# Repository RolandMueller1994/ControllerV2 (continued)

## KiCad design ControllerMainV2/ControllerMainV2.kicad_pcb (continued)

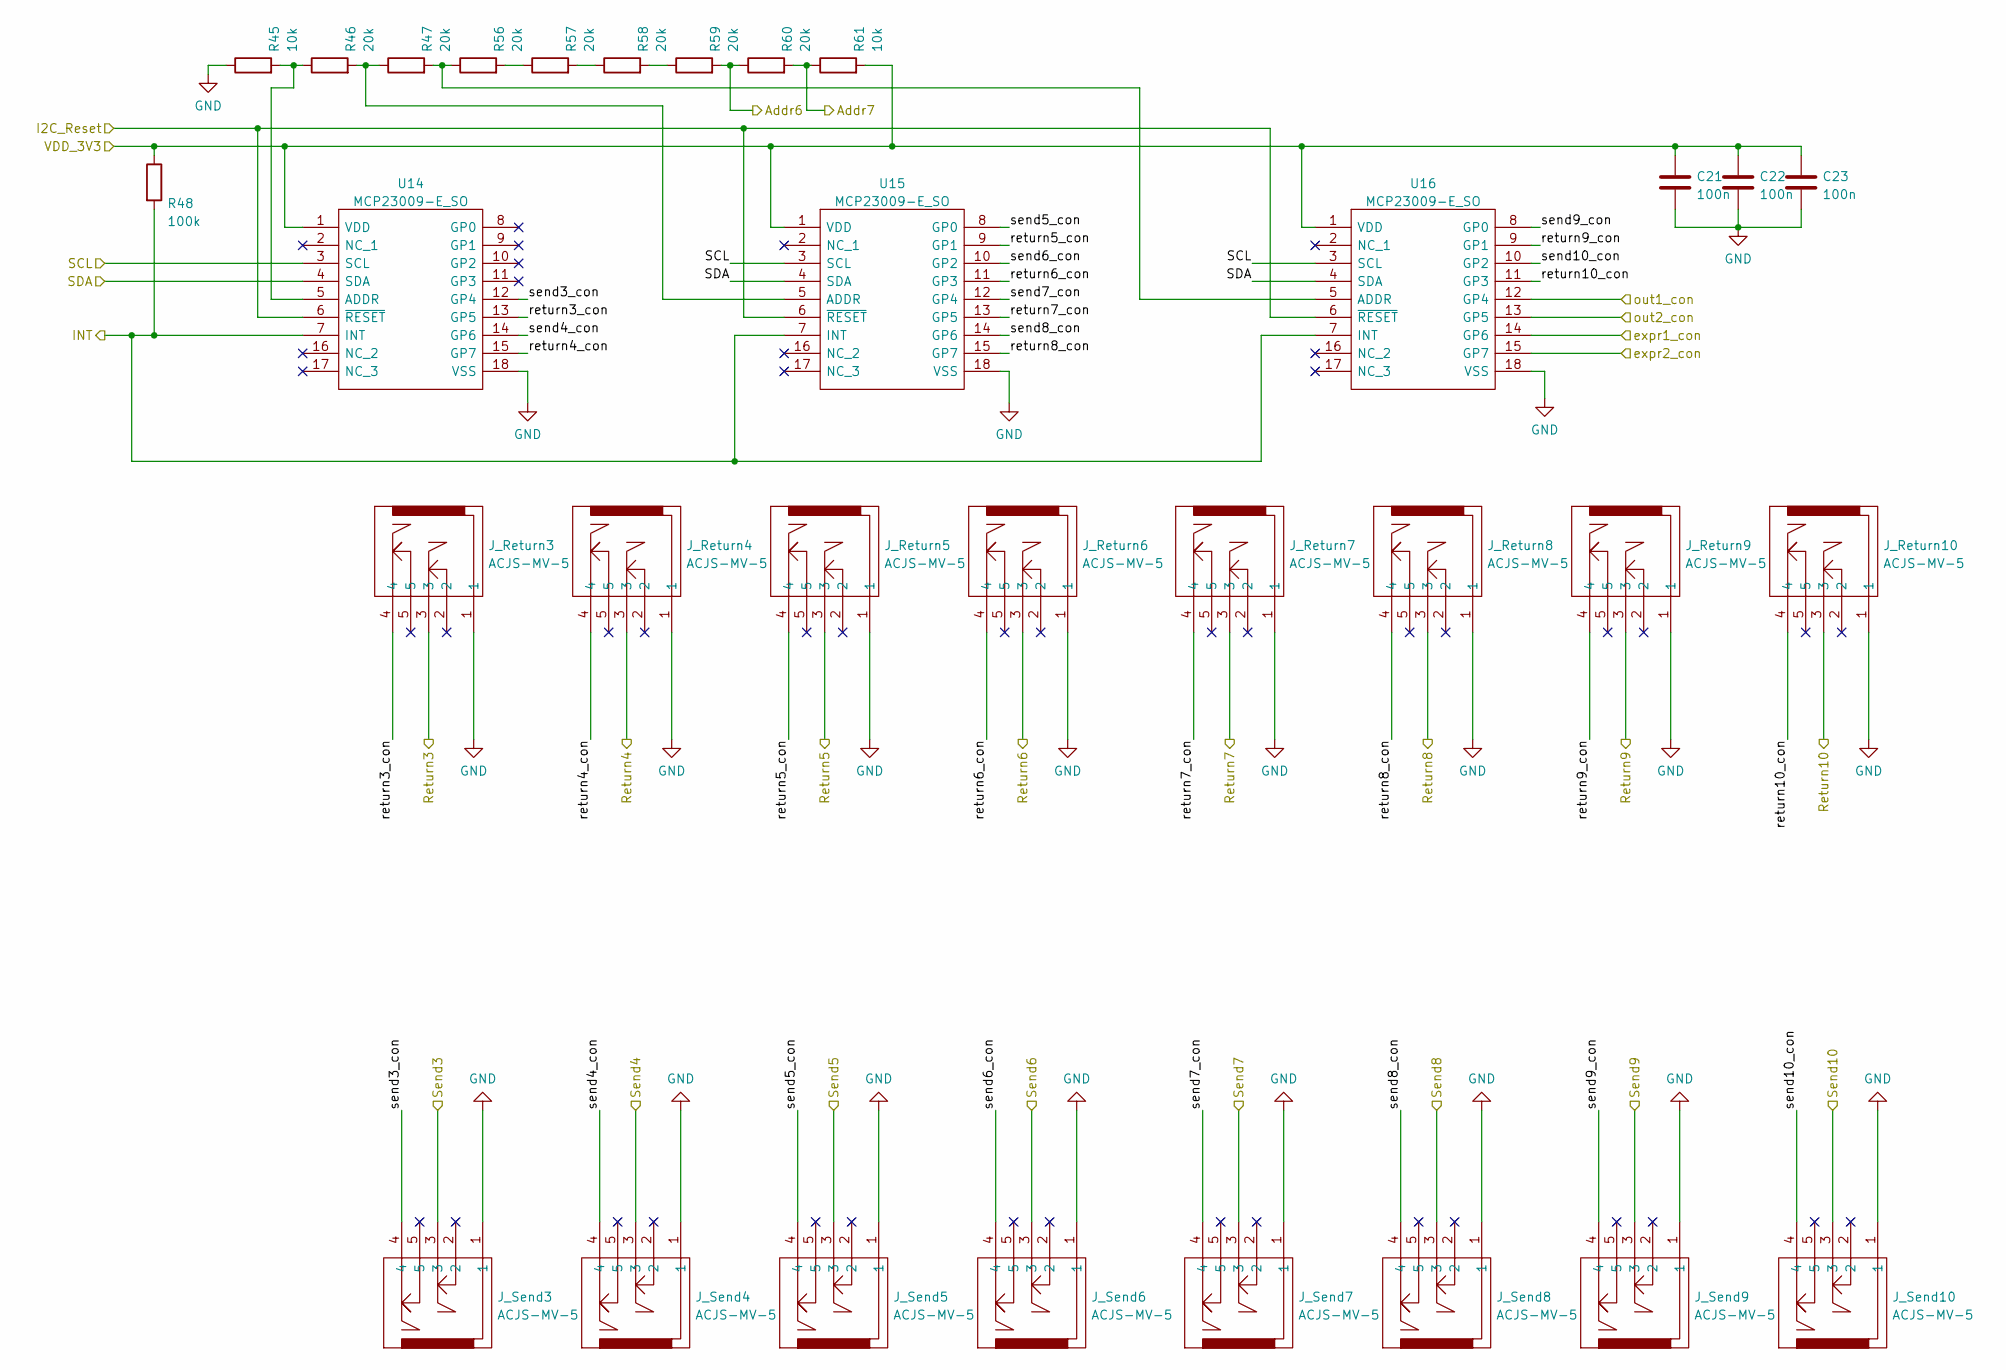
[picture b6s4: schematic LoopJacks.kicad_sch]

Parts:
C21, C22, C23: 100n; C_1206_3216Metric_Pad1.33x1.80mm_HandSolder
J_Return3, J_Return4, J_Return5, J_Return6, J_Return7, J_Return8, J_Return9, J_Return10: ACJS-MV-5; ACJSMV5; Manufacturer_Part_Number ACJS-MV-5; Mouser Part Number 523-ACJS-MV-5
J_Send3, J_Send4, J_Send5, J_Send6, J_Send7, J_Send8, J_Send9, J_Send10: ACJS-MV-5; ACJSMV5; Manufacturer_Part_Number ACJS-MV-5; Mouser Part Number 523-ACJS-MV-5
R45, R61: 10k; R_1206_3216Metric_Pad1.30x1.75mm_HandSolder
R46, R47, R56, R57, R58, R59, R60: 20k; R_1206_3216Metric_Pad1.30x1.75mm_HandSolder
R48: 100k; R_1206_3216Metric_Pad1.30x1.75mm_HandSolder
U14, U15, U16: MCP23009-E_SO; SOIC127P1030X265-18N; Manufacturer_Part_Number MCP23009-E/SO; Mouser Part Number 579-MCP23009-E/SO

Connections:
/Addr6: R59.2, R60.1; also elsewhere on the board
/Addr7: R60.2, R61.1; also elsewhere on the board
/INT: R48.2, U14.7 (INT), U15.7 (INT), U16.7 (INT); also elsewhere on the board
/LoopJacks/expr1_con: U16.14 (GP6); also elsewhere on the board
/LoopJacks/expr2_con: U16.15 (GP7); also elsewhere on the board
/LoopJacks/out1_con: U16.12 (GP4); also elsewhere on the board
/LoopJacks/out2_con: U16.13 (GP5); also elsewhere on the board
/LoopJacks/return3_con: J_Return3.4, U14.13 (GP5)
/LoopJacks/return4_con: J_Return4.4, U14.15 (GP7)
/LoopJacks/return5_con: J_Return5.4, U15.9 (GP1)
/LoopJacks/return6_con: J_Return6.4, U15.11 (GP3)
/LoopJacks/return7_con: J_Return7.4, U15.13 (GP5)
/LoopJacks/return8_con: J_Return8.4, U15.15 (GP7)
/LoopJacks/return9_con: J_Return9.4, U16.9 (GP1)
/LoopJacks/return10_con: J_Return10.4, U16.11 (GP3)
/LoopJacks/send3_con: J_Send3.4, U14.12 (GP4)
/LoopJacks/send4_con: J_Send4.4, U14.14 (GP6)
/LoopJacks/send5_con: J_Send5.4, U15.8 (GP0)
/LoopJacks/send6_con: J_Send6.4, U15.10 (GP2)
/LoopJacks/send7_con: J_Send7.4, U15.12 (GP4)
/LoopJacks/send8_con: J_Send8.4, U15.14 (GP6)
/LoopJacks/send9_con: J_Send9.4, U16.8 (GP0)
/LoopJacks/send10_con: J_Send10.4, U16.10 (GP2)
/SCL: U14.3 (SCL), U15.3 (SCL), U16.3 (SCL); also elsewhere on the board
/SDA: U14.4 (SDA), U15.4 (SDA), U16.4 (SDA); also elsewhere on the board
/return3: J_Return3.3; also elsewhere on the board
/return4: J_Return4.3; also elsewhere on the board
/return5: J_Return5.3; also elsewhere on the board
/return6: J_Return6.3; also elsewhere on the board
/return7: J_Return7.3; also elsewhere on the board
/return8: J_Return8.3; also elsewhere on the board
/return9: J_Return9.3; also elsewhere on the board
/return10: J_Return10.3; also elsewhere on the board
/send3: J_Send3.3; also elsewhere on the board
/send4: J_Send4.3; also elsewhere on the board
/send5: J_Send5.3; also elsewhere on the board
/send6: J_Send6.3; also elsewhere on the board
/send7: J_Send7.3; also elsewhere on the board
/send8: J_Send8.3; also elsewhere on the board
/send9: J_Send9.3; also elsewhere on the board
/send10: J_Send10.3; also elsewhere on the board
unnamed: R45.2, R46.1, U14.5 (ADDR)
unnamed: R46.2, R47.1, U15.5 (ADDR)
unnamed: R47.2, R56.1, U16.5 (ADDR)
unnamed: R56.2, R57.1
unnamed: R57.2, R58.1
unnamed: R58.2, R59.1

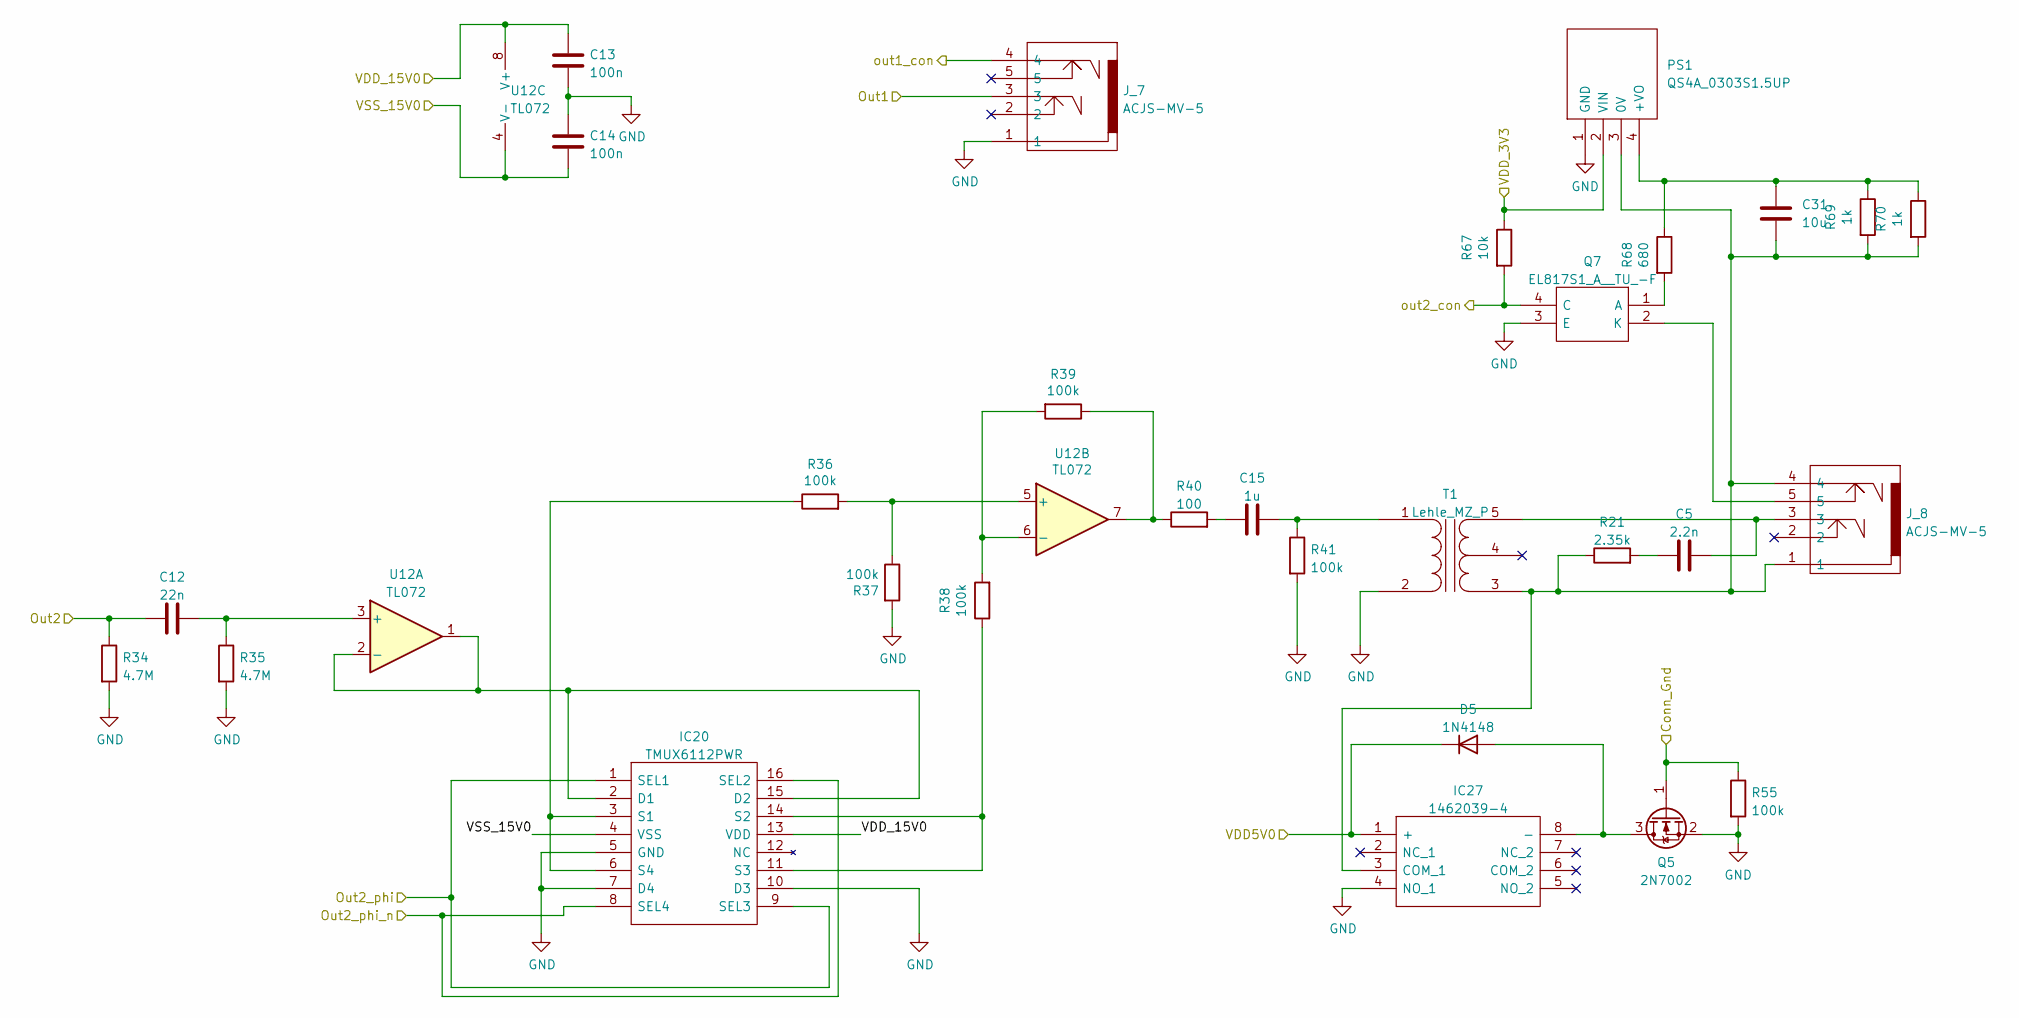
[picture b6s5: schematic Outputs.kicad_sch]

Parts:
C5: 2.2n; C_1206_3216Metric_Pad1.33x1.80mm_HandSolder
C12: 22n; C_1206_3216Metric_Pad1.33x1.80mm_HandSolder
C13, C14: 100n; C_1206_3216Metric_Pad1.33x1.80mm_HandSolder
C15: 1u; C_1206_3216Metric_Pad1.33x1.80mm_HandSolder
C31: 10u; C_1206_3216Metric_Pad1.33x1.80mm_HandSolder
D5: 1N4148; D_SOD-123
IC20: TMUX6112PWR; SOP65P640X120-16N; Manufacturer_Part_Number TMUX6112PWR; Mouser Part Number 595-TMUX6112PWR
IC27: 1462039-4; 14620394; Manufacturer_Part_Number 1462039-4; Mouser Part Number 655-1462039-4
J_7, J_8: ACJS-MV-5; ACJSMV5; Manufacturer_Part_Number ACJS-MV-5; Mouser Part Number 523-ACJS-MV-5
PS1: QS4A_0303S1.5UP; QS4A_1.5UP; Manufacturer_Part_Number QS4A_0303S1.5UP
Q5: 2N7002; SOT-23
Q7: EL817S1_A__TU_-F; SOP254P1030X390-4N; Manufacturer_Part_Number EL817S1(A)(TU)-F
R21: 2.35k; R_1206_3216Metric_Pad1.30x1.75mm_HandSolder
R34, R35: 4.7M; R_1206_3216Metric_Pad1.30x1.75mm_HandSolder
R36, R37, R38, R39, R41, R55: 100k; R_1206_3216Metric_Pad1.30x1.75mm_HandSolder
R40: 100; R_1206_3216Metric_Pad1.30x1.75mm_HandSolder
R67: 10k; R_1206_3216Metric_Pad1.30x1.75mm_HandSolder
R68: 680; R_1206_3216Metric_Pad1.30x1.75mm_HandSolder
R69, R70: 1k; R_1206_3216Metric_Pad1.30x1.75mm_HandSolder
T1: Lehle_MZ_P
U12: TL072; SOIC127P600X175-8N

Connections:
/LoopJacks/out1_con: J_7.4; also elsewhere on the board
/LoopJacks/out2_con: Q7.4 (C), R67.2; also elsewhere on the board
/Out2_phi: IC20.1 (SEL1), IC20.9 (SEL3); also elsewhere on the board
/Out2_phi_n: IC20.8 (SEL4), IC20.16 (SEL2); also elsewhere on the board
/Outputs/Conn_Gnd: Q5.1 (G), R55.1; also elsewhere on the board
/out1: J_7.3; also elsewhere on the board
/out2: C12.1, R34.1; also elsewhere on the board
unnamed: C5.1, J_8.3, T1.5 (SB)
unnamed: C5.2, R21.2
unnamed: C12.2, R35.1, U12.3 (+)
unnamed: C15.1, R40.2
unnamed: C15.2, R41.1, T1.1 (AA)
unnamed: C31.1, IC27.3 (COM_1), J_8.1, J_8.4, PS1.3 (0V), R21.1, R69.2, R70.2, T1.3 (SA)
unnamed: C31.2, PS1.4 (+VO), R68.1, R69.1, R70.1
unnamed: D5.2 (A), IC27.8 (-), Q5.3 (D)
unnamed: IC20.3 (S1), IC20.6 (S4), R36.1
unnamed: IC20.11 (S3), IC20.14 (S2), R38.1
unnamed: IC20.2 (D1), IC20.15 (D2), U12.1, U12.2 (-)
unnamed: J_8.5, Q7.2 (K)
unnamed: Q7.1 (A), R68.2
unnamed: R36.2, R37.1, U12.5 (+)
unnamed: R38.2, R39.2, U12.6 (-)
unnamed: R39.1, R40.1, U12.7

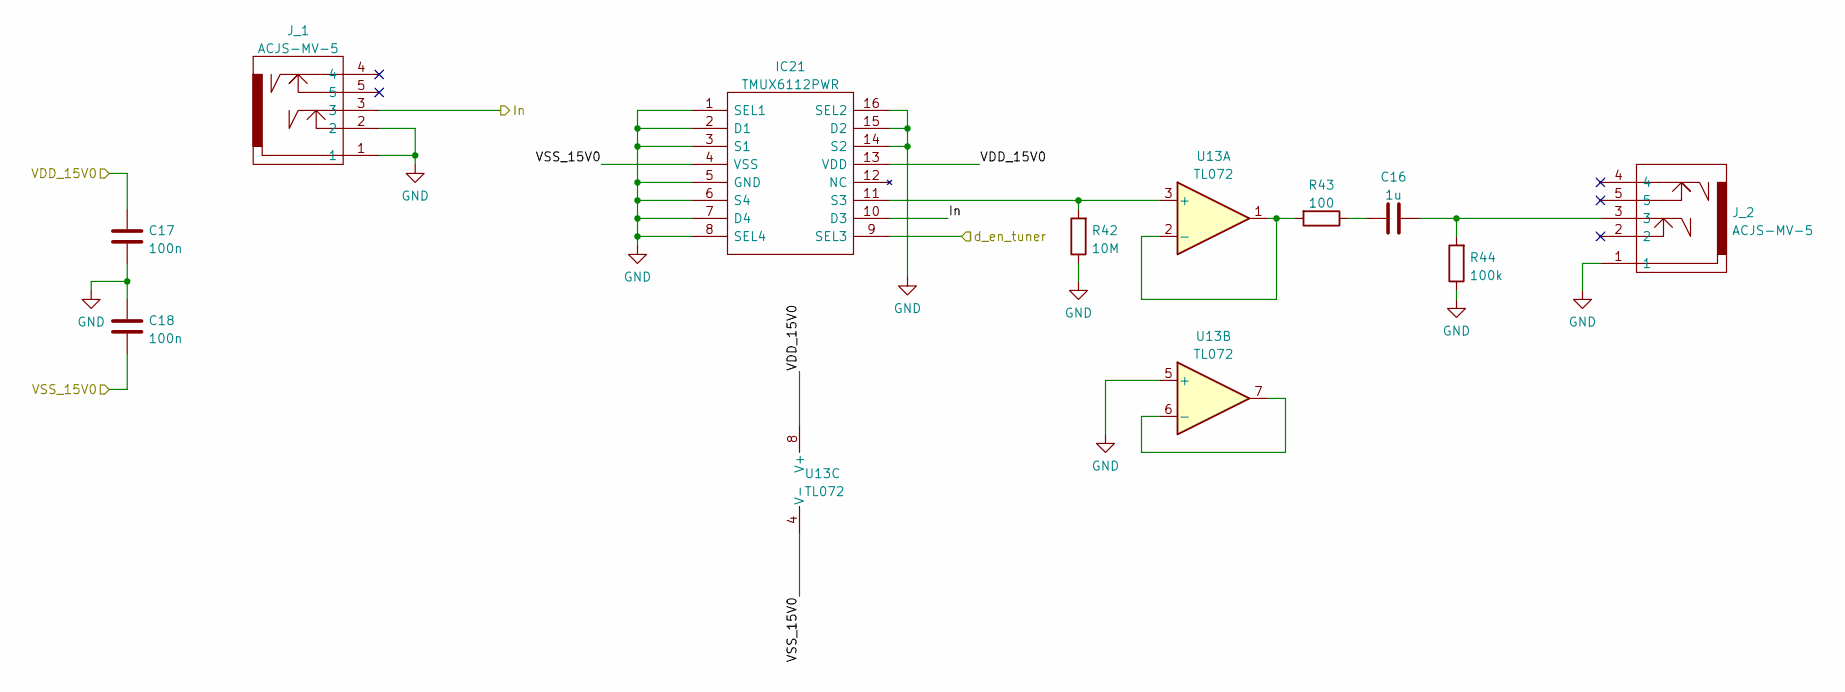
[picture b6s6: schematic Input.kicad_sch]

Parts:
C16: 1u; C_1206_3216Metric_Pad1.33x1.80mm_HandSolder
C17, C18: 100n; C_1206_3216Metric_Pad1.33x1.80mm_HandSolder
IC21: TMUX6112PWR; SOP65P640X120-16N; Manufacturer_Part_Number TMUX6112PWR; Mouser Part Number 595-TMUX6112PWR
J_1, J_2: ACJS-MV-5; ACJSMV5; Manufacturer_Part_Number ACJS-MV-5; Mouser Part Number 523-ACJS-MV-5
R42: 10M; R_1206_3216Metric_Pad1.30x1.75mm_HandSolder
R43: 100; R_1206_3216Metric_Pad1.30x1.75mm_HandSolder
R44: 100k; R_1206_3216Metric_Pad1.30x1.75mm_HandSolder
U13: TL072; SOIC127P600X175-8N

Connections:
/Tuner: IC21.9 (SEL3); also elsewhere on the board
/in: IC21.10 (D3), J_1.3; also elsewhere on the board
unnamed: C16.1, R43.1
unnamed: C16.2, J_2.3, R44.2
unnamed: IC21.11 (S3), R42.2, U13.3 (+)
unnamed: R43.2, U13.1, U13.2 (-)
unnamed: U13.6 (-), U13.7

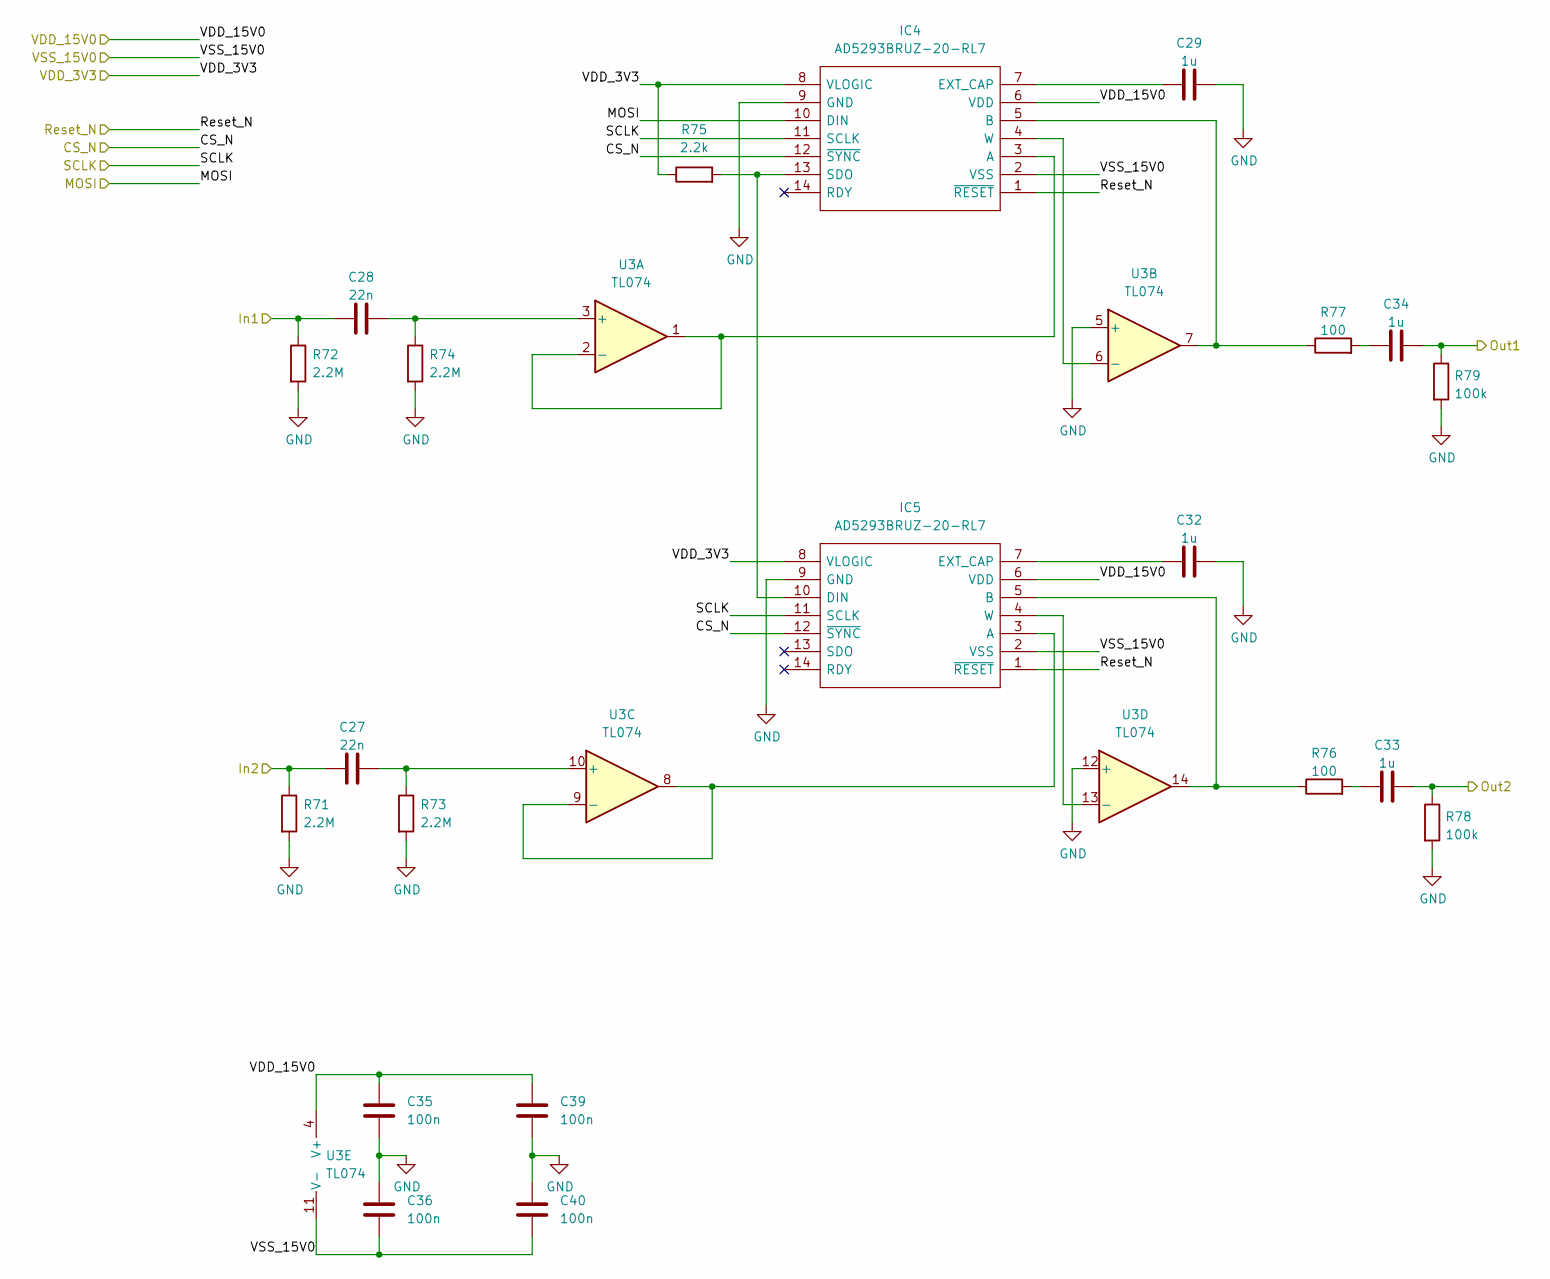
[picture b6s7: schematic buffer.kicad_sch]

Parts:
C27, C28: 22n; C_1206_3216Metric_Pad1.33x1.80mm_HandSolder
C29, C32, C33, C34: 1u; C_1206_3216Metric_Pad1.33x1.80mm_HandSolder
C35, C36, C39, C40: 100n; C_1206_3216Metric_Pad1.33x1.80mm_HandSolder
IC4, IC5: AD5293BRUZ-20-RL7; SOP65P640X120-14N; Manufacturer_Part_Number AD5293BRUZ-20-RL7; Mouser Part Number 584-AD5293BRUZ-20-R7
R71, R72, R73, R74: 2.2M; R_1206_3216Metric_Pad1.30x1.75mm_HandSolder
R75: 2.2k; R_1206_3216Metric_Pad1.30x1.75mm_HandSolder
R76, R77: 100; R_1206_3216Metric_Pad1.30x1.75mm_HandSolder
R78, R79: 100k; R_1206_3216Metric_Pad1.30x1.75mm_HandSolder
U3: TL074; SOIC127P600X175-14N

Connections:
/MOSI: IC4.10 (DIN); also elsewhere on the board
/SCLK: IC4.11 (SCLK), IC5.11 (SCLK); also elsewhere on the board
/amp1: C28.1, R72.1; also elsewhere on the board
/amp1_out: C34.2, R79.1; also elsewhere on the board
/amp2: C27.1, R71.1; also elsewhere on the board
/amp2_out: C33.2, R78.1; also elsewhere on the board
unnamed: C27.2, R73.1, U3.10 (+)
unnamed: C28.2, R74.1, U3.3 (+)
unnamed: C29.1, IC4.7 (EXT_CAP)
unnamed: C32.1, IC5.7 (EXT_CAP)
unnamed: C33.1, R76.2
unnamed: C34.1, R77.2
unnamed: IC4.3 (A), U3.1, U3.2 (-)
unnamed: IC4.4 (W), U3.6 (-)
unnamed: IC4.5 (B), R77.1, U3.7
unnamed: IC4.13 (SDO), IC5.10 (DIN), R75.2
unnamed: IC5.3 (A), U3.8, U3.9 (-)
unnamed: IC5.4 (W), U3.13 (-)
unnamed: IC5.5 (B), R76.1, U3.14

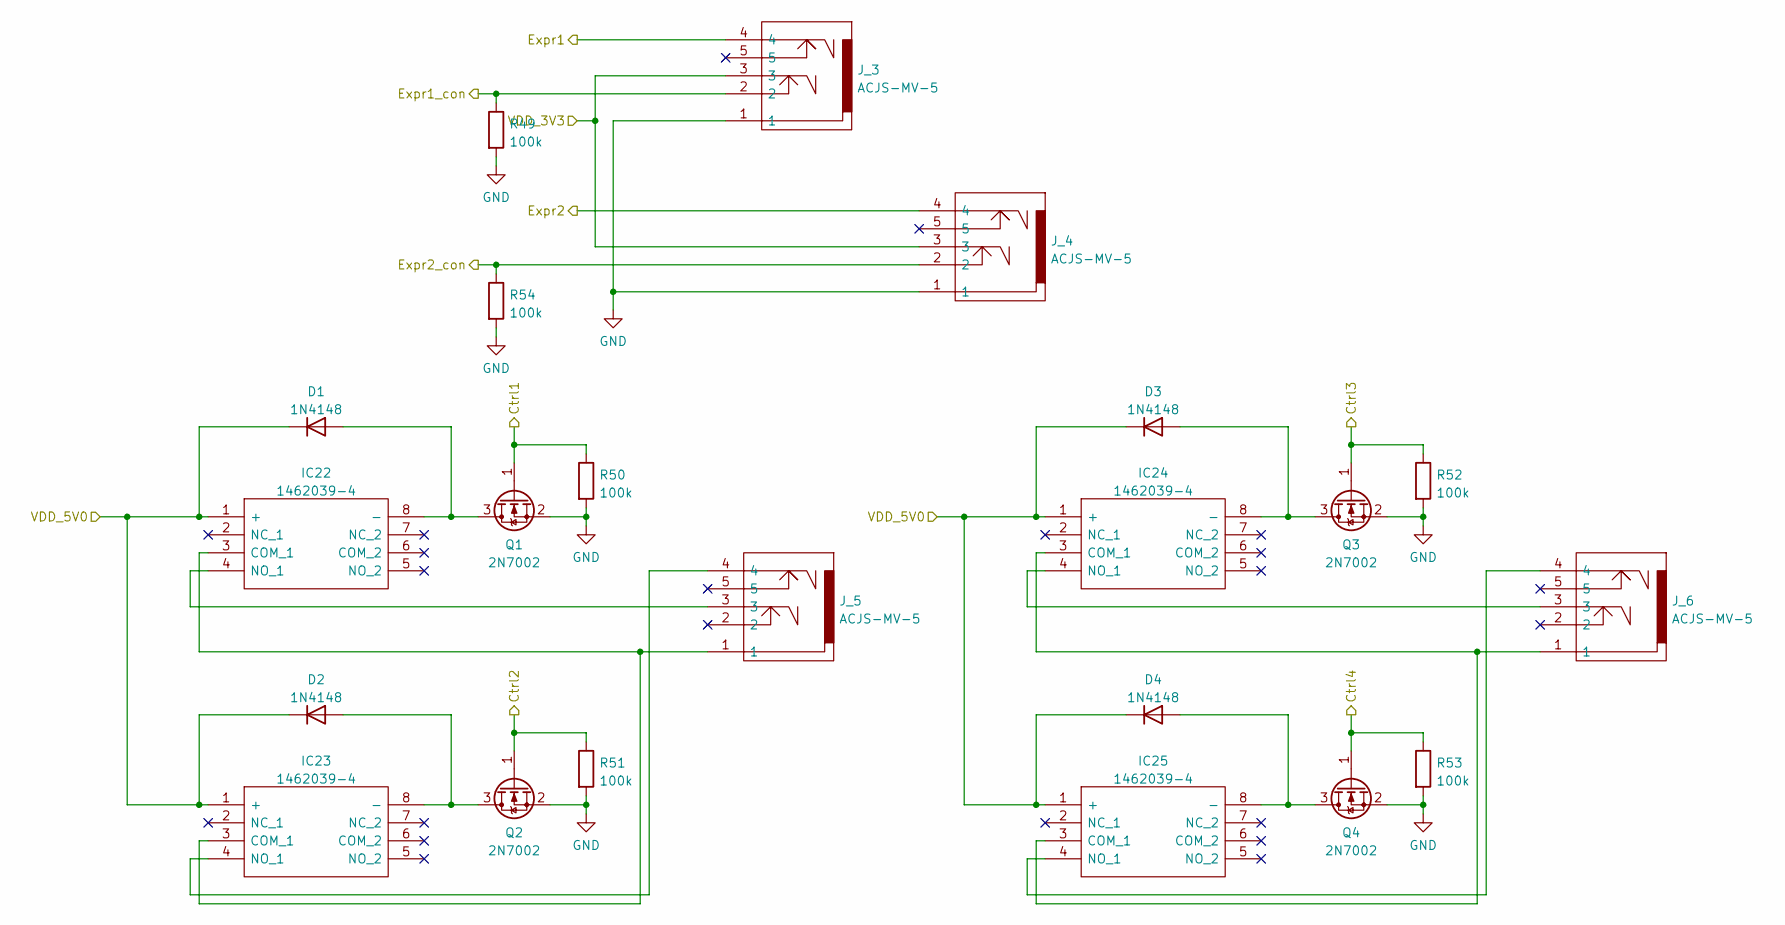
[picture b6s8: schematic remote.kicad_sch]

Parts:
D1, D2, D3, D4: 1N4148; D_SOD-123
IC22, IC23, IC24, IC25: 1462039-4; 14620394; Manufacturer_Part_Number 1462039-4; Mouser Part Number 655-1462039-4
J_3, J_4, J_5, J_6: ACJS-MV-5; ACJSMV5; Manufacturer_Part_Number ACJS-MV-5; Mouser Part Number 523-ACJS-MV-5
Q1, Q2, Q3, Q4: 2N7002; SOT-23
R49, R50, R51, R52, R53, R54: 100k; R_1206_3216Metric_Pad1.30x1.75mm_HandSolder

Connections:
/Ctrl1: Q1.1 (G), R50.1; also elsewhere on the board
/Ctrl2: Q2.1 (G), R51.1; also elsewhere on the board
/Ctrl3: Q3.1 (G), R52.1; also elsewhere on the board
/Ctrl4: Q4.1 (G), R53.1; also elsewhere on the board
/LoopJacks/expr1_con: J_3.2, R49.1; also elsewhere on the board
/LoopJacks/expr2_con: J_4.2, R54.1; also elsewhere on the board
/expr1: J_3.4; also elsewhere on the board
/expr2: J_4.4; also elsewhere on the board
unnamed: D1.2 (A), IC22.8 (-), Q1.3 (D)
unnamed: D2.2 (A), IC23.8 (-), Q2.3 (D)
unnamed: D3.2 (A), IC24.8 (-), Q3.3 (D)
unnamed: D4.2 (A), IC25.8 (-), Q4.3 (D)
unnamed: IC22.3 (COM_1), IC23.3 (COM_1), J_5.1
unnamed: IC22.4 (NO_1), J_5.3
unnamed: IC23.4 (NO_1), J_5.4
unnamed: IC24.3 (COM_1), IC25.3 (COM_1), J_6.1
unnamed: IC24.4 (NO_1), J_6.3
unnamed: IC25.4 (NO_1), J_6.4

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
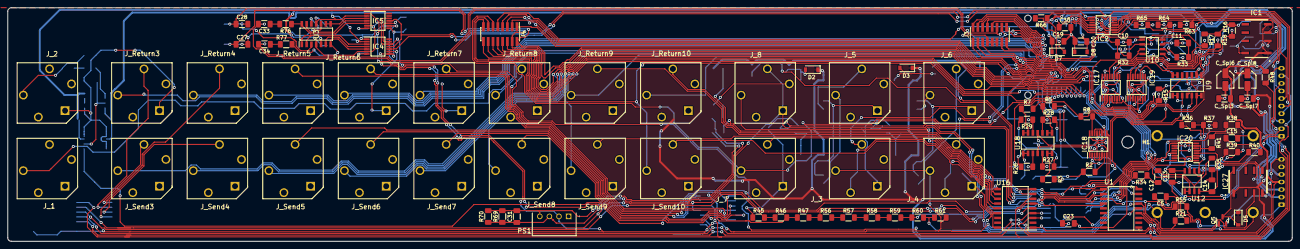
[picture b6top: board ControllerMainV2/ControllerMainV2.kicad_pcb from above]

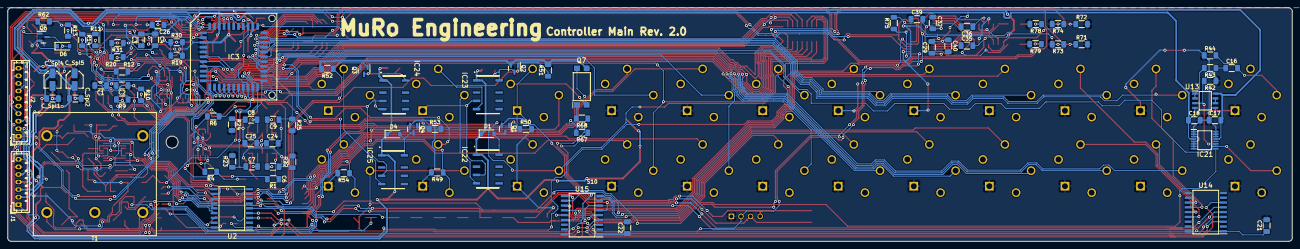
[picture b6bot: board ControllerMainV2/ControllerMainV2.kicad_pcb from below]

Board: 2 copper layers, 340.0 x 61.8 mm, 197 parts (84 on the bottom side), 169 nets.

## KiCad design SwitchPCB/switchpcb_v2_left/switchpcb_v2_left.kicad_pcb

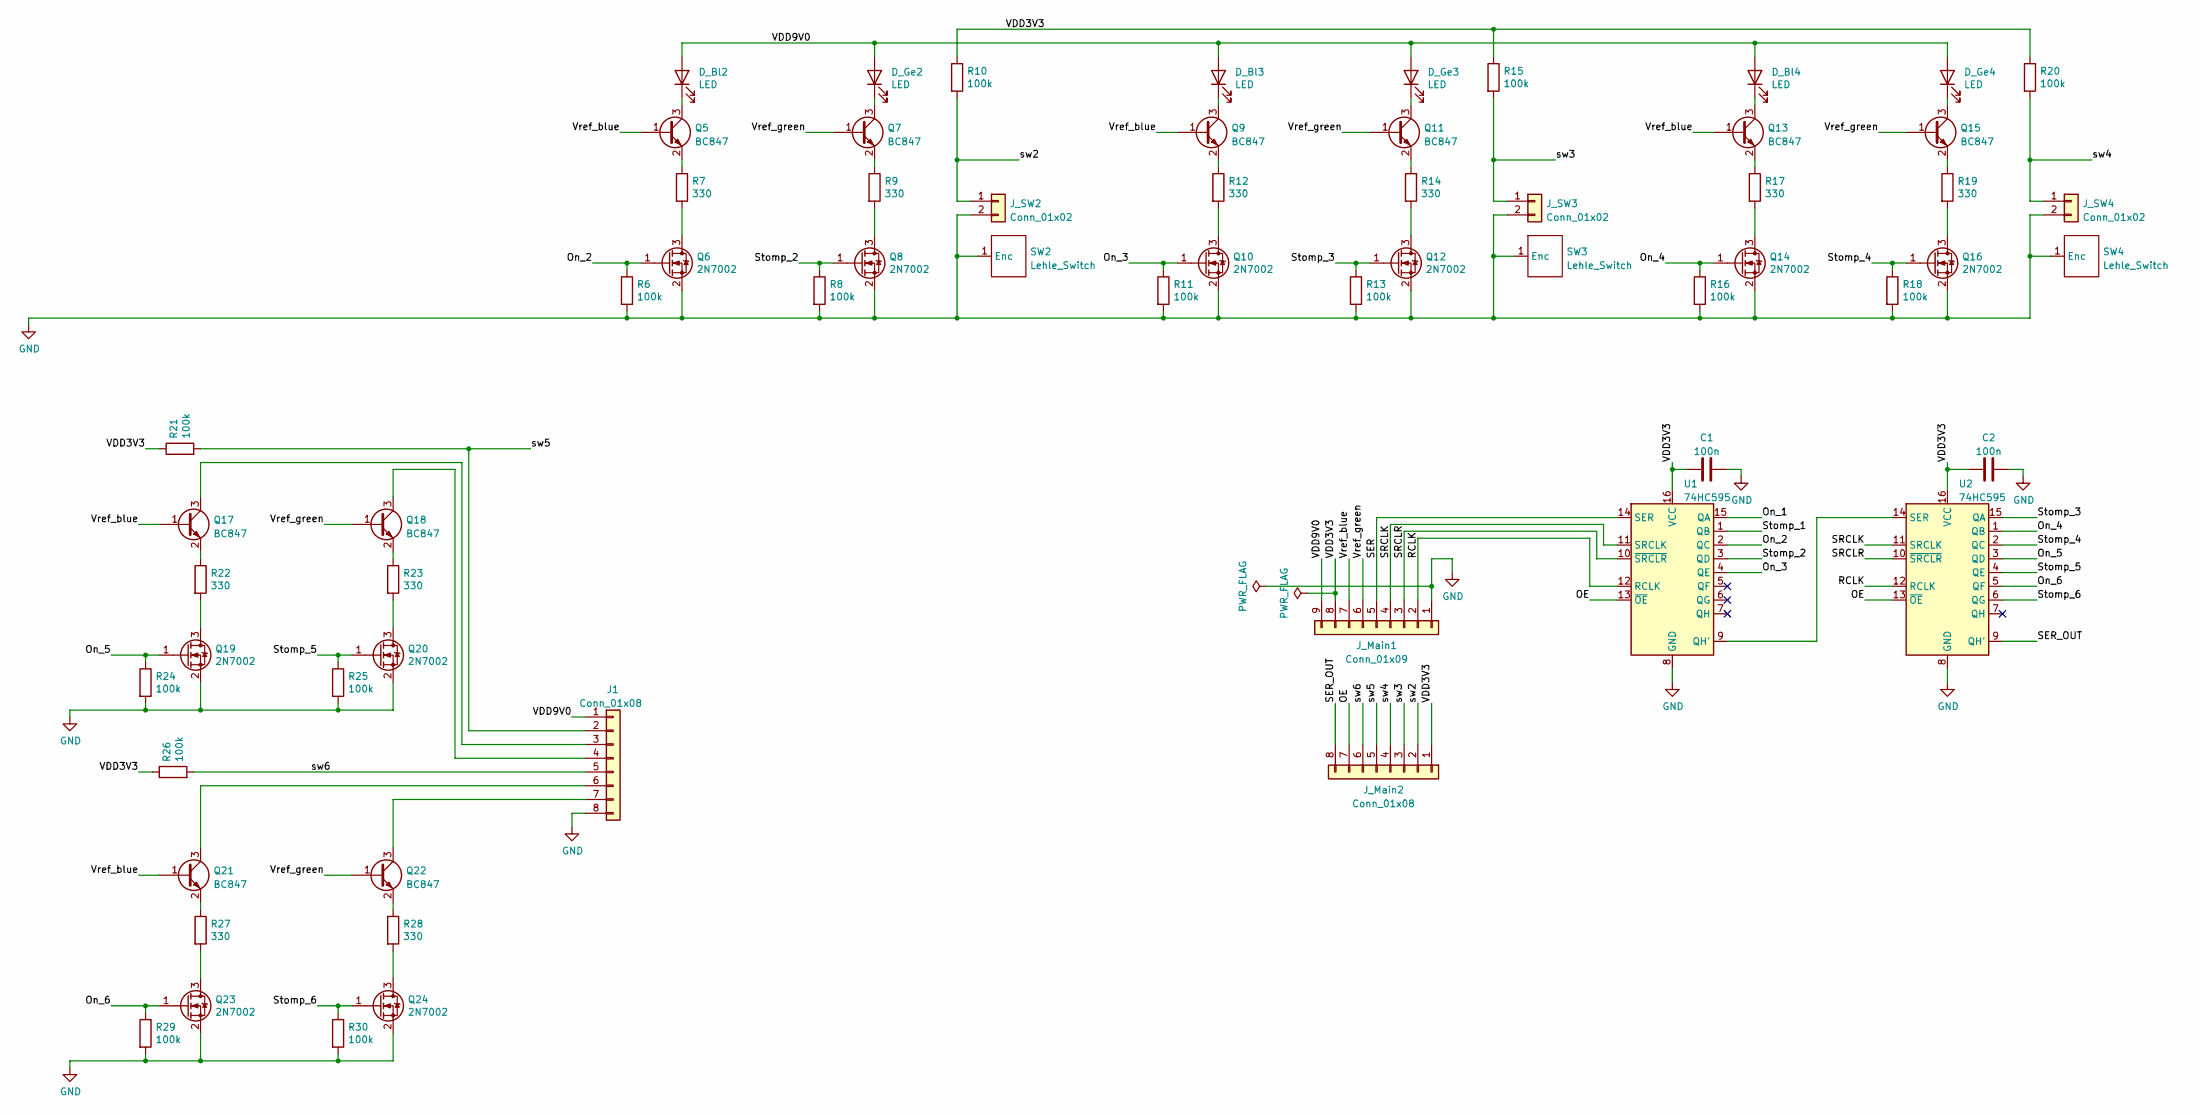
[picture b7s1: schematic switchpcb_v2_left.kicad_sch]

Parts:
C1, C2: 100n; C_1206_3216Metric_Pad1.33x1.80mm_HandSolder
D_Bl2, D_Bl3, D_Bl4: LED; LED_D3.0mm
D_Ge2, D_Ge3, D_Ge4: LED; LED_D3.0mm
J1: Conn_01x08; JST_PH_B8B-PH-K_1x08_P2.00mm_Vertical
J_Main1: Conn_01x09; JST_PH_B9B-PH-K_1x09_P2.00mm_Vertical
J_Main2: Conn_01x08; JST_PH_B8B-PH-K_1x08_P2.00mm_Vertical
J_SW2, J_SW3, J_SW4: Conn_01x02; JST_PH_B2B-PH-K_1x02_P2.00mm_Vertical
Q5, Q7, Q9, Q11, Q13, Q15, Q17, Q18, Q21, Q22: BC847; SOT-23
Q6, Q8, Q10, Q12, Q14, Q16, Q19, Q20, Q23, Q24: 2N7002; SOT-23
R6, R8, R10, R11, R13, R15, R16, R18, R20, R21, R24, R25, R26, R29, R30: 100k; R_1206_3216Metric_Pad1.30x1.75mm_HandSolder
R7, R9, R12, R14, R17, R19, R22, R23, R27, R28: 330; R_1206_3216Metric_Pad1.30x1.75mm_HandSolder
SW2, SW3, SW4: Lehle_Switch; LehleSwitch
U1, U2: 74HC595; SOIC127P600X175-16N

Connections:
/OE: J_Main2.7, U1.13 (~OE), U2.13 (~OE)
/On_1: U1.15 (QA)
/On_2: Q6.1 (G), R6.1, U1.2 (QC)
/On_3: Q10.1 (G), R11.1, U1.4 (QE)
/On_4: Q14.1 (G), R16.1, U2.1 (QB)
/On_5: Q19.1 (G), R24.1, U2.3 (QD)
/On_6: Q23.1 (G), R29.1, U2.5 (QF)
/RCLK: J_Main1.2, U1.12 (RCLK), U2.12 (RCLK)
/SER: J_Main1.5, U1.14 (SER)
/SER_OUT: J_Main2.8, U2.9 (QH')
/SRCLK: J_Main1.4, U1.11 (SRCLK), U2.11 (SRCLK)
/SRCLR: J_Main1.3, U1.10 (~SRCLR), U2.10 (~SRCLR)
/Stomp_1: U1.1 (QB)
/Stomp_2: Q8.1 (G), R8.1, U1.3 (QD)
/Stomp_3: Q12.1 (G), R13.1, U2.15 (QA)
/Stomp_4: Q16.1 (G), R18.1, U2.2 (QC)
/Stomp_5: Q20.1 (G), R25.1, U2.4 (QE)
/Stomp_6: Q24.1 (G), R30.1, U2.6 (QG)
/VDD3V3: C1.1, C2.1, J_Main1.8, J_Main2.1, R10.1, R15.1, R20.1, R21.1, R26.1, U1.16 (VCC), U2.16 (VCC)
/VDD9V0: D_Bl2.2 (A), D_Bl3.2 (A), D_Bl4.2 (A), D_Ge2.2 (A), D_Ge3.2 (A), D_Ge4.2 (A), J1.1, J_Main1.9
/Vref_blue: J_Main1.7, Q5.1 (B), Q9.1 (B), Q13.1 (B), Q17.1 (B), Q21.1 (B)
/Vref_green: J_Main1.6, Q7.1 (B), Q11.1 (B), Q15.1 (B), Q18.1 (B), Q22.1 (B)
/sw2: J_Main2.2, J_SW2.1, R10.2
/sw3: J_Main2.3, J_SW3.1, R15.2
/sw4: J_Main2.4, J_SW4.1, R20.2
/sw5: J1.2, J_Main2.5, R21.2
/sw6: J1.5, J_Main2.6, R26.2
GND: C1.2, C2.2, J1.8, J_Main1.1, J_SW2.2, J_SW3.2, J_SW4.2, Q6.2 (S), Q8.2 (S), Q10.2 (S), Q12.2 (S), Q14.2 (S), Q16.2 (S), Q19.2 (S), Q20.2 (S), Q23.2 (S), Q24.2 (S), R6.2, R8.2, R11.2, R13.2, R16.2, R18.2, R24.2, R25.2, R29.2, R30.2, SW2.1 (Enc), SW3.1 (Enc), SW4.1 (Enc), U1.8 (GND), U2.8 (GND)
unnamed: D_Bl2.1 (K), Q5.3 (C)
unnamed: D_Bl3.1 (K), Q9.3 (C)
unnamed: D_Bl4.1 (K), Q13.3 (C)
unnamed: D_Ge2.1 (K), Q7.3 (C)
unnamed: D_Ge3.1 (K), Q11.3 (C)
unnamed: D_Ge4.1 (K), Q15.3 (C)
unnamed: J1.3, Q17.3 (C)
unnamed: J1.4, Q18.3 (C)
unnamed: J1.6, Q21.3 (C)
unnamed: J1.7, Q22.3 (C)
unnamed: Q5.2 (E), R7.1
unnamed: Q6.3 (D), R7.2
unnamed: Q7.2 (E), R9.1
unnamed: Q8.3 (D), R9.2
unnamed: Q9.2 (E), R12.1
unnamed: Q10.3 (D), R12.2
unnamed: Q11.2 (E), R14.1
unnamed: Q12.3 (D), R14.2
unnamed: Q13.2 (E), R17.1
unnamed: Q14.3 (D), R17.2
unnamed: Q15.2 (E), R19.1
unnamed: Q16.3 (D), R19.2
unnamed: Q17.2 (E), R22.1
unnamed: Q18.2 (E), R23.1
unnamed: Q19.3 (D), R22.2
unnamed: Q20.3 (D), R23.2
unnamed: Q21.2 (E), R27.1
unnamed: Q22.2 (E), R28.1
unnamed: Q23.3 (D), R27.2
unnamed: Q24.3 (D), R28.2
unnamed: U1.9 (QH'), U2.14 (SER)

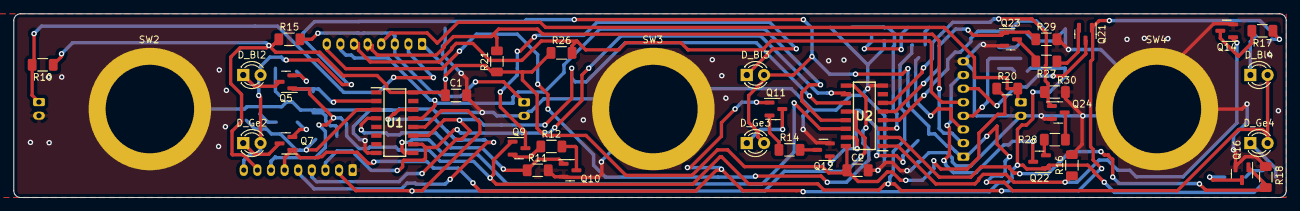
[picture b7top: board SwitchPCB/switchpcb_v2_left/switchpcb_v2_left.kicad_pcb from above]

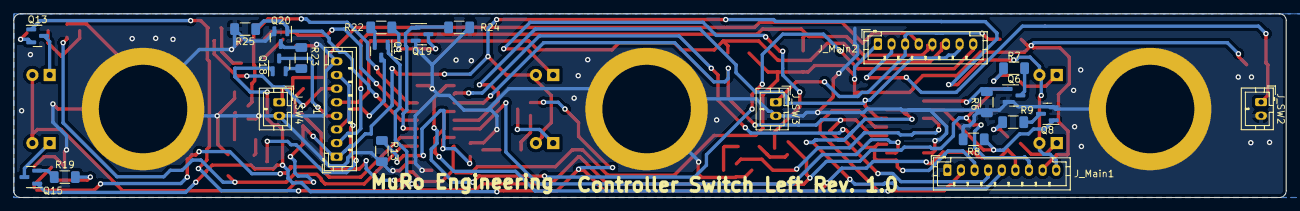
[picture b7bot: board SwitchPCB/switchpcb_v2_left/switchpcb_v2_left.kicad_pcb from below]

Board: 2 copper layers, 187.0 x 27.0 mm, 64 parts (24 on the bottom side), 57 nets.

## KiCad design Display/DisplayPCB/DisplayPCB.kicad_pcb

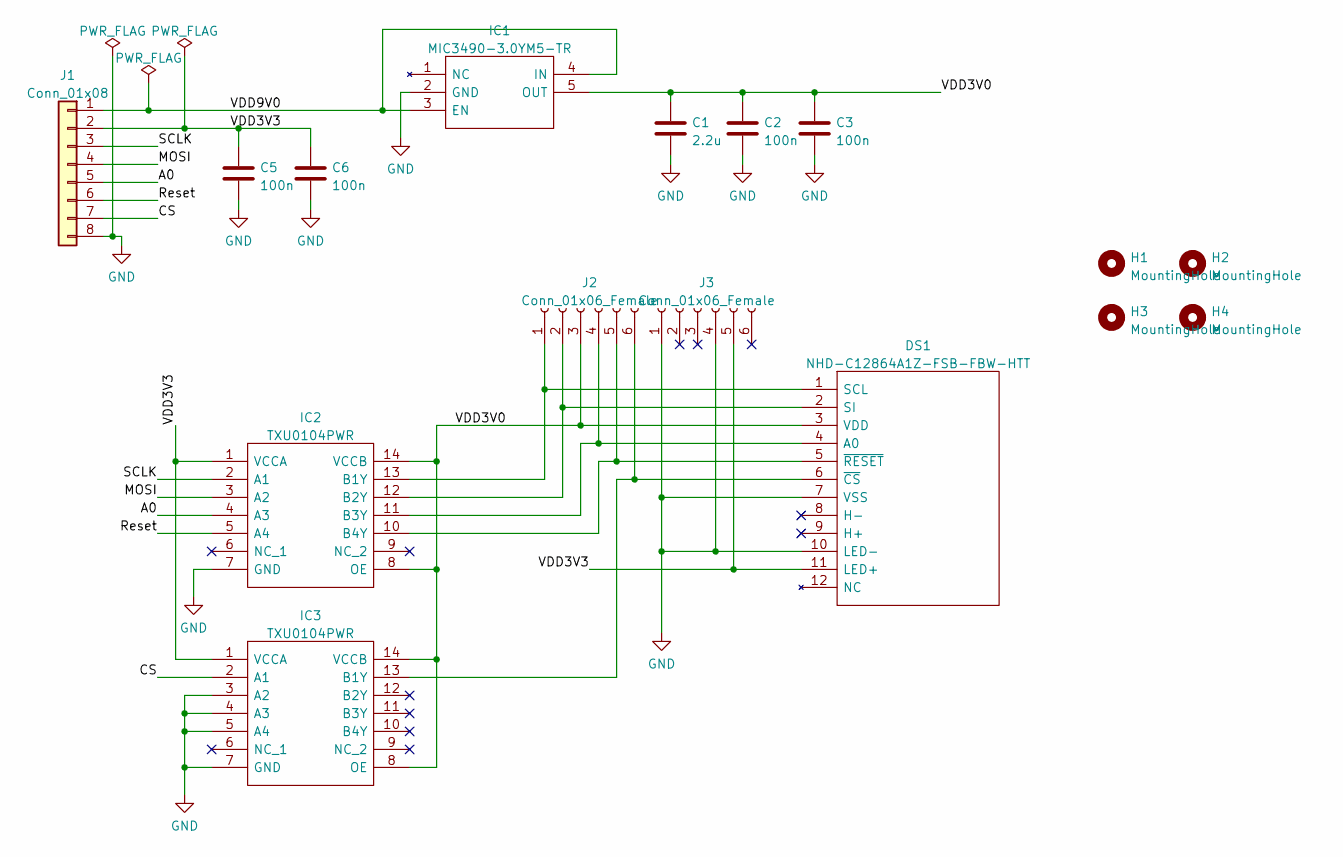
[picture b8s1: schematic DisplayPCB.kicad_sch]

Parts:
C1: 2.2u; C_1206_3216Metric_Pad1.33x1.80mm_HandSolder
C2, C3, C5, C6: 100n; C_1206_3216Metric_Pad1.33x1.80mm_HandSolder
DS1: NHD-C12864A1Z-FSB-FBW-HTT; NHDC12864A1ZFSBFBWHTT; Manufacturer_Part_Number NHD-C12864A1Z-FSB-FBW-HTT; Mouser Part Number 763-C12864A1ZFSBFBWH
H1, H2, H3, H4: MountingHole; MountingHole_3.2mm_M3
IC1: MIC3490-3.0YM5-TR; SOT95P280X145-5N; Manufacturer_Part_Number MIC3490-3.0YM5-TR; Mouser Part Number 579-MIC349030YM5TR
IC2, IC3: TXU0104PWR; SOP65P640X120-14N; Manufacturer_Part_Number TXU0104PWR; Mouser Part Number 595-TXU0104PWR
J1: Conn_01x08; JST_PH_B8B-PH-K_1x08_P2.00mm_Vertical
J2, J3: Conn_01x06_Female; PinHeader_1x06_P2.54mm_Vertical

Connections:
/A0: IC2.4 (A3), J1.5
/CS: IC3.2 (A1), J1.7
/MOSI: IC2.3 (A2), J1.4
/Reset: IC2.5 (A4), J1.6
/SCLK: IC2.2 (A1), J1.3
/VDD3V0: C1.1, C2.1, C3.1, DS1.3 (VDD), IC1.5 (OUT), IC2.8 (OE), IC2.14 (VCCB), IC3.8 (OE), IC3.14 (VCCB), J2.3
/VDD3V3: C5.1, C6.1, DS1.11 (LED+), IC2.1 (VCCA), IC3.1 (VCCA), J1.2, J3.5
/VDD9V0: IC1.3 (EN), IC1.4 (IN), J1.1
GND: C1.2, C2.2, C3.2, C5.2, C6.2, DS1.7 (VSS), DS1.10 (LED-), IC1.2 (GND), IC2.7 (GND), IC3.3 (A2), IC3.4 (A3), IC3.5 (A4), IC3.7 (GND), J1.8, J3.1, J3.4
unnamed: DS1.1 (SCL), IC2.13 (B1Y), J2.1
unnamed: DS1.2 (SI), IC2.12 (B2Y), J2.2
unnamed: DS1.4 (A0), IC2.11 (B3Y), J2.4
unnamed: DS1.5 (~RESET), IC2.10 (B4Y), J2.5
unnamed: DS1.6 (~CS), IC3.13 (B1Y), J2.6
